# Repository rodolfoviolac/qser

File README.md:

# QSER

QSER is a application and hardware shield interface to manage and fully control a engine motor (Quanser Robots) on Galileo v2 shield.
On this repository you will find the shield hardware design under `/shield` and the software resources under `/src`.

## Build

### Project Local 
This project is using cmake to automate build releases and versioning.
- Compile the full project with `/cmake-build-release/make`.
- Clean built files with `/cmake-build-release/make clean`.

### Project Target Galileo
- Compile the full project with `make`.
- Clean built files with `make clean`.

### Documentation
Compile the project documentation to `docs/` folder.
```
  $ make docs
```

## Modules

#### Debugger:
This project contain a built in debugger for handling execution path helping the developers find out eventual bugs or errors.
To enable this feature you need to enable the debugger options under `/src/helpers/helpers.h`.

#### Run Local:
This project contain a local template simulation to help developers simulate the code that will run on the Galileo shield, this feature enable developers to build and run the code without the physical shield device. 
To enable this feature you need to enable the Run Local option under `/src/helpers/helpers.h`.

## Roadmap

See the [open issues](https://github.com/rodolfoviolac/qser/issues) for a list of proposed features (and known issues).

## Contributing

For major changes, please open an issue first to discuss what you would like to change.
Please make sure to update tests as appropriate.

1. Fork the Project
2. Create your Feature Branch (`git checkout -b feature/AmazingFeature`)
3. Commit your Changes (`git commit -m 'Add some AmazingFeature'`)
4. Push to the Branch (`git push origin feature/AmazingFeature`)
5. Open a Pull Request

## Team

> Or Contributors

| <a href="https://github.com/rodolfoviolac" target="_blank">**Rodolfo Viola**</a> | <a href="https://github.com/gazillmer" target="_blank">**Gabriel Zillmer**</a> | <a href="https://github.com/felipefuhr" target="_blank">**Felipe Fuhr**</a> |
| :---: |:---:| :---:|
|     |  |   |
| <a href="https://github.com/rodolfoviolac" target="_blank">`github.com/rodolfoviolac`</a> | <a href="https://github.com/gazillmer" target="_blank">`github.com/gazillmer`</a> | <a href="https://github.com/felipefuhr" target="_blank">`github.com/felipefuhr`</a> |

## License
[MIT](https://github.com/rodolfoviolac/qser/LICENSE.md)

Project Link: [https://github.com/rodolfoviolac/qser](https://github.com/rodolfoviolac/qser)

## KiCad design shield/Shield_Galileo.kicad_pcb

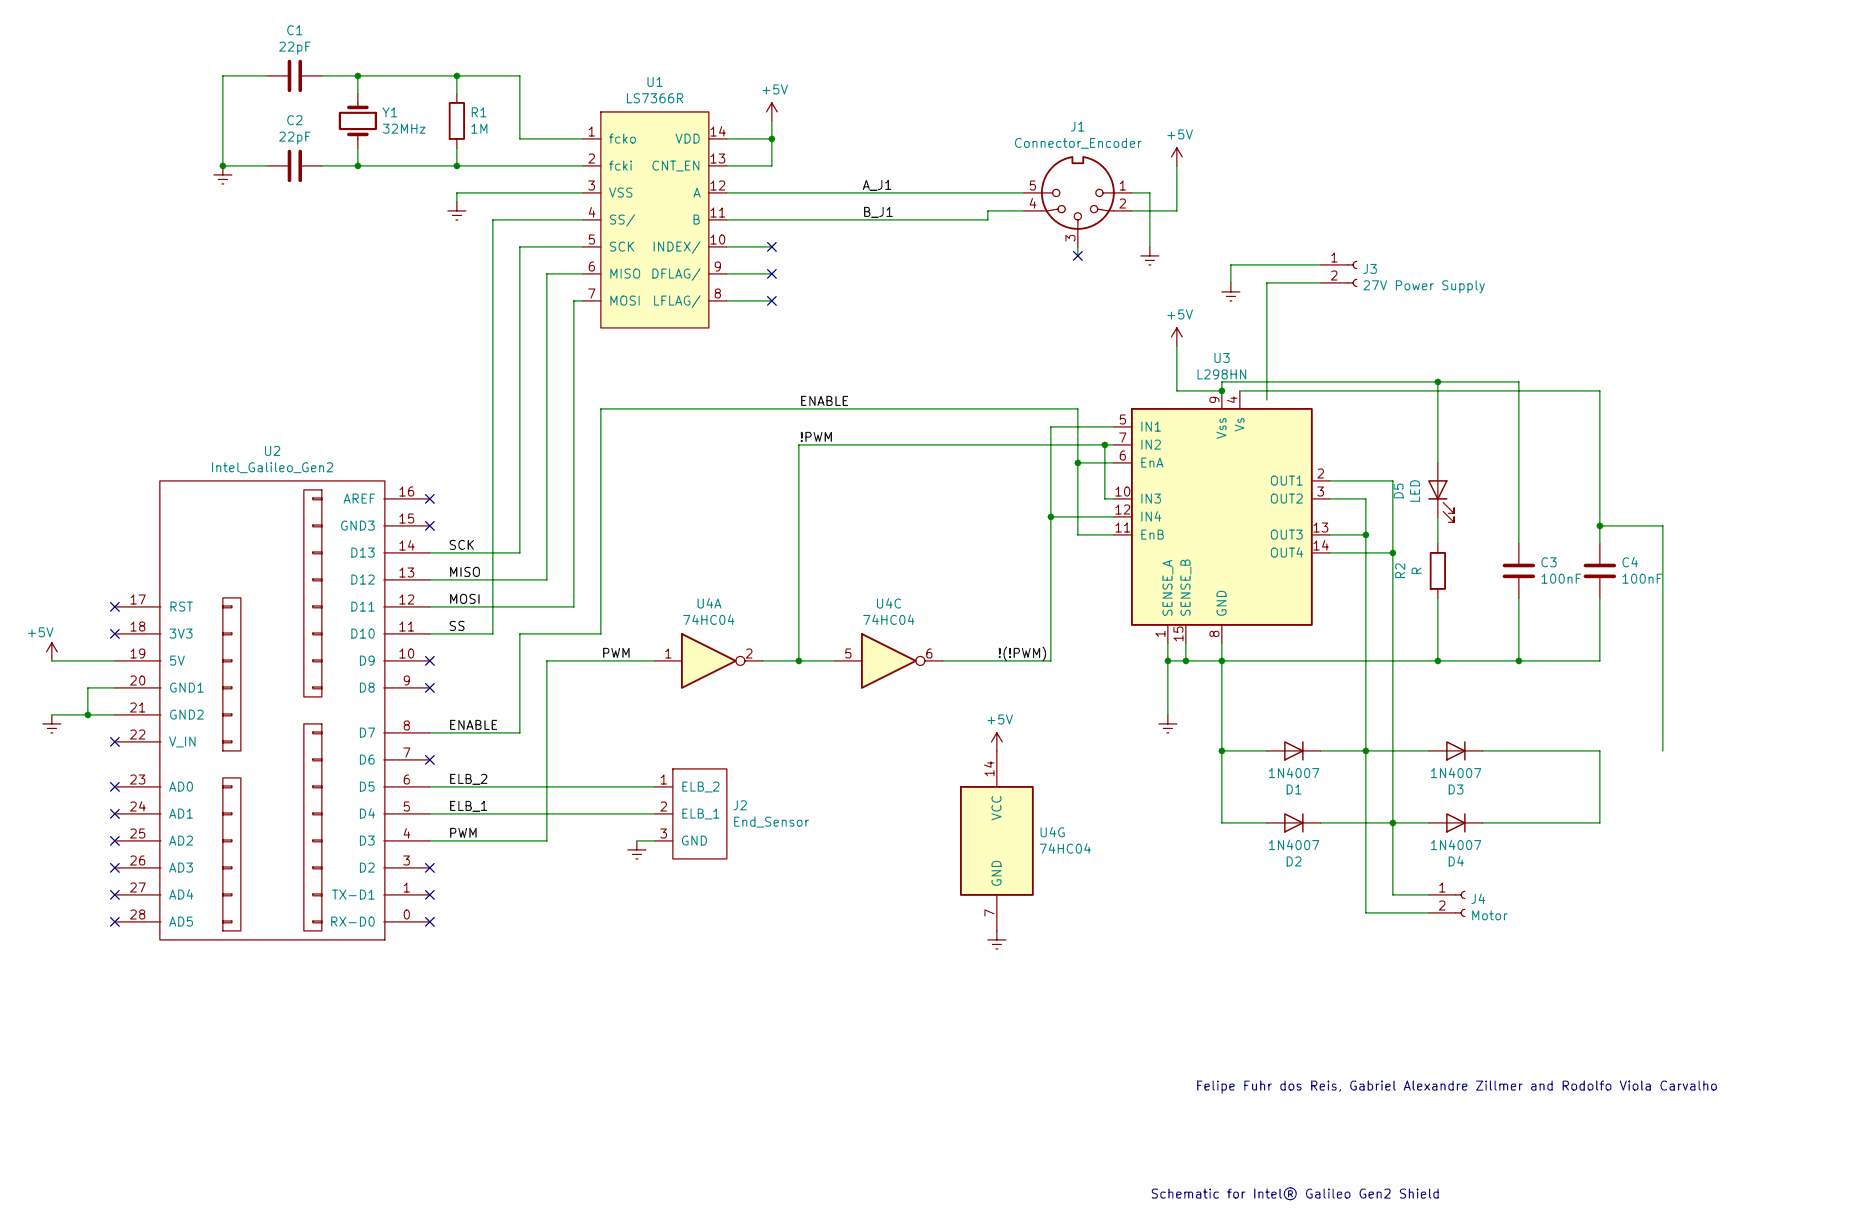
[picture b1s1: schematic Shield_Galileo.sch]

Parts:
C1, C2: 22pF; C_Disc_D3.0mm_W2.0mm_P2.50mm
C3, C4: 100nF; C_Disc_D10.5mm_W5.0mm_P7.50mm
D1, D2, D3, D4: 1N4007; D_DO-41_SOD81_P10.16mm_Horizontal
D5: LED; LED_D5.0mm
J1: Connector_Encoder; PinHeader_1x05_P2.54mm_Vertical
J2: End_Sensor; PinHeader_1x03_P2.54mm_Vertical
J3: 27V Power Supply; TerminalBlock_Altech_AK300-2_P5.00mm
J4: Motor; TerminalBlock_Altech_AK300-2_P5.00mm
R1: 1M; R_Axial_DIN0204_L3.6mm_D1.6mm_P5.08mm_Horizontal
R2: R; R_Axial_DIN0204_L3.6mm_D1.6mm_P5.08mm_Horizontal
U1: LS7366R; DIP-14_W7.62mm
U2: Intel_Galileo_Gen2; Intel_Galileo_Gen2_Pins
U3: L298HN; TO127P2020X500X2100-15
U4: 74HC04; DIP-14_W7.62mm
Y1: 32MHz; Crystal_HC52-6mm_Vertical

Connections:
+5V: C3.1, D5.2 (A), J1.2, U1.13 (CNT_EN), U1.14 (VDD), U2.19 (5V), U3.9 (Vss), U4.14 (VCC)
/!(!PWM): U3.5 (IN1), U3.12 (IN4), U4.6
/!PWM: U3.7 (IN2), U3.10 (IN3), U4.2, U4.5
/A_J1: J1.5, U1.12 (A)
/B_J1: J1.4, U1.11 (B)
/ELB_1: J2.2 (ELB_1), U2.5 (D4)
/ELB_2: J2.1 (ELB_2), U2.6 (D5)
/ENABLE: U2.8 (D7), U3.6 (EnA), U3.11 (EnB)
/MISO: U1.6 (MISO), U2.13 (D12)
/MOSI: U1.7 (MOSI), U2.12 (D11)
/PWM: U2.4 (D3), U4.1
/SCK: U1.5 (SCK), U2.14 (D13)
/SS: U1.4 (SS/), U2.11 (D10)
Earth: C1.2, C2.2, C3.2, C4.2, D1.2 (A), D2.2 (A), J1.1, J2.3 (GND), J3.1, R2.2, U1.3 (VSS), U2.20 (GND1), U2.21 (GND2), U3.1 (SENSE_A), U3.8 (GND), U3.15 (SENSE_B), U4.7 (GND)
unnamed: C1.1, R1.1, U1.1 (fcko), Y1.1
unnamed: C2.1, R1.2, U1.2 (fcki), Y1.2
unnamed: D1.1 (K), D3.2 (A), J4.2, U3.3 (OUT2), U3.13 (OUT3)
unnamed: D2.1 (K), D4.2 (A), J4.1, U3.2 (OUT1), U3.14 (OUT4)
unnamed: D3.1 (K), D4.1 (K)
unnamed: D5.1 (K), R2.1

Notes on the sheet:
Felipe Fuhr dos Reis, Gabriel Alexandre Zillmer and Rodolfo Viola Carvalho
Schematic for Intel® Galileo Gen2 Shield

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
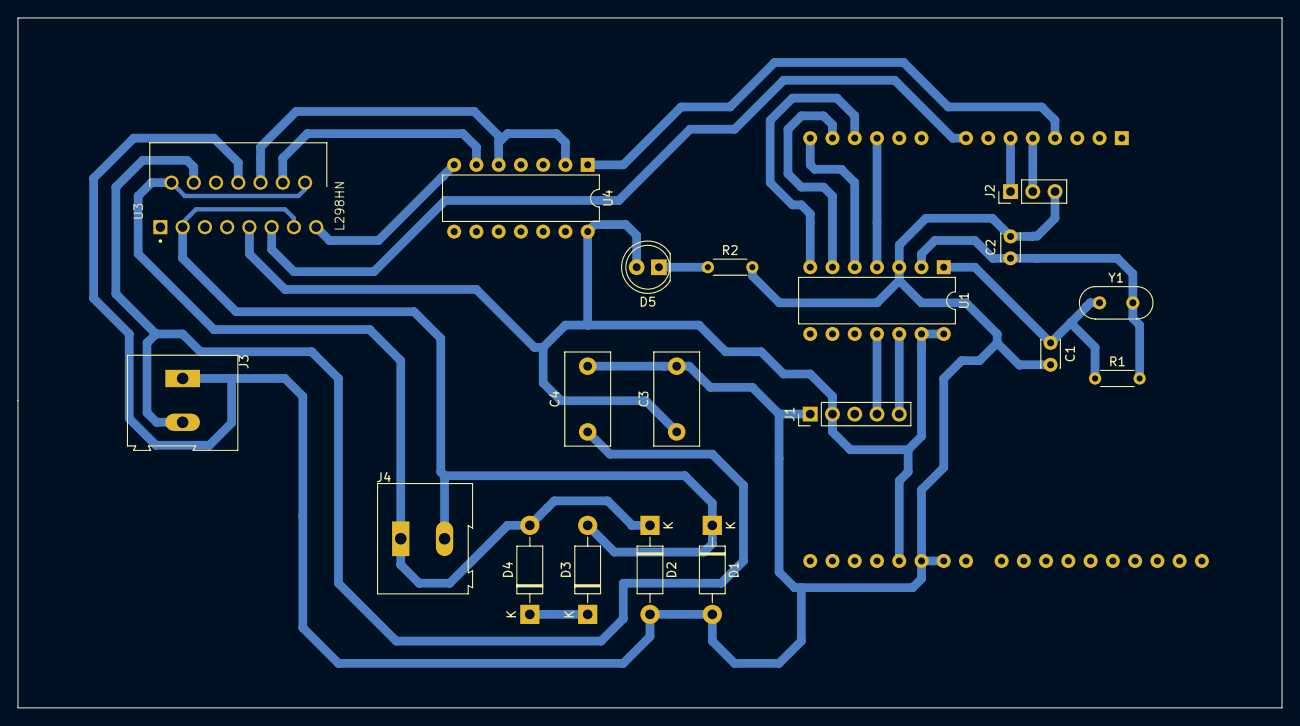
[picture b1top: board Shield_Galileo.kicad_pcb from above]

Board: 2 copper layers, 144.3 x 78.7 mm, 20 parts (1 on the bottom side), 21 nets.

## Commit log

2019-11-23 git ignore
2019-11-23 ignore cmake-build-debug
2019-11-23 Added scripts and initialization scripts pins
2019-11-23 Added Main Thread and Scripts To Build Files
2019-11-23 Added User Options Switch
2019-11-23 Added amount value to speed
2019-11-23 Added write to file for handling writing & quancer interface
2019-11-23 Added Lots of Functions
2019-11-24 Added handler for two switches and make file for galileo
2019-11-24 Added JPL Read Command
2019-11-24 Added Doxygen Files Documentation
2019-11-24 minor doxygen leftover
2019-11-26 Added break function and fix problem with jpl functions
2019-11-26 Add schematic and PCB layout
2019-11-26 Starting Readme Documentation
2019-11-26 Build Docs and Added More Stuff to readme
2019-11-26 fix miss spelling on readme
2019-11-27 Add new Shield files
2019-11-29 Change PWM from io6 to io7. Minor changes on init script
2019-12-01 Added PID Controller
2019-12-01 Added PID handler to change voltage
2019-12-01 Initializer Qser Function and Started Decoder
2019-12-01 TurnOff PID missing on JPL and added decoder to makefile
2019-12-01 Fix makefile miss spelling path
2019-12-01 Minor changes on readme
2019-12-02 Added Decoder Interface Module
2019-12-02 Added Command Interface to Decoder
2019-12-02 Added new Cover Image
2019-12-06 Added step change speed motor
2019-12-11 Started Documentation
2019-12-11 Helpers Documentation
2019-12-11 Main Thread And Fix Minor Changes
2019-12-11 Added More Documentation
2019-12-11 Novo Build Do Docs
2019-12-11 Changed Basic Files Names
2019-12-11 Added More Comments
2019-12-11 New Docs PT
2019-12-11 Remain File
2019-12-12 Added Rads Conversion Values
2019-12-12 Added Remain Files
